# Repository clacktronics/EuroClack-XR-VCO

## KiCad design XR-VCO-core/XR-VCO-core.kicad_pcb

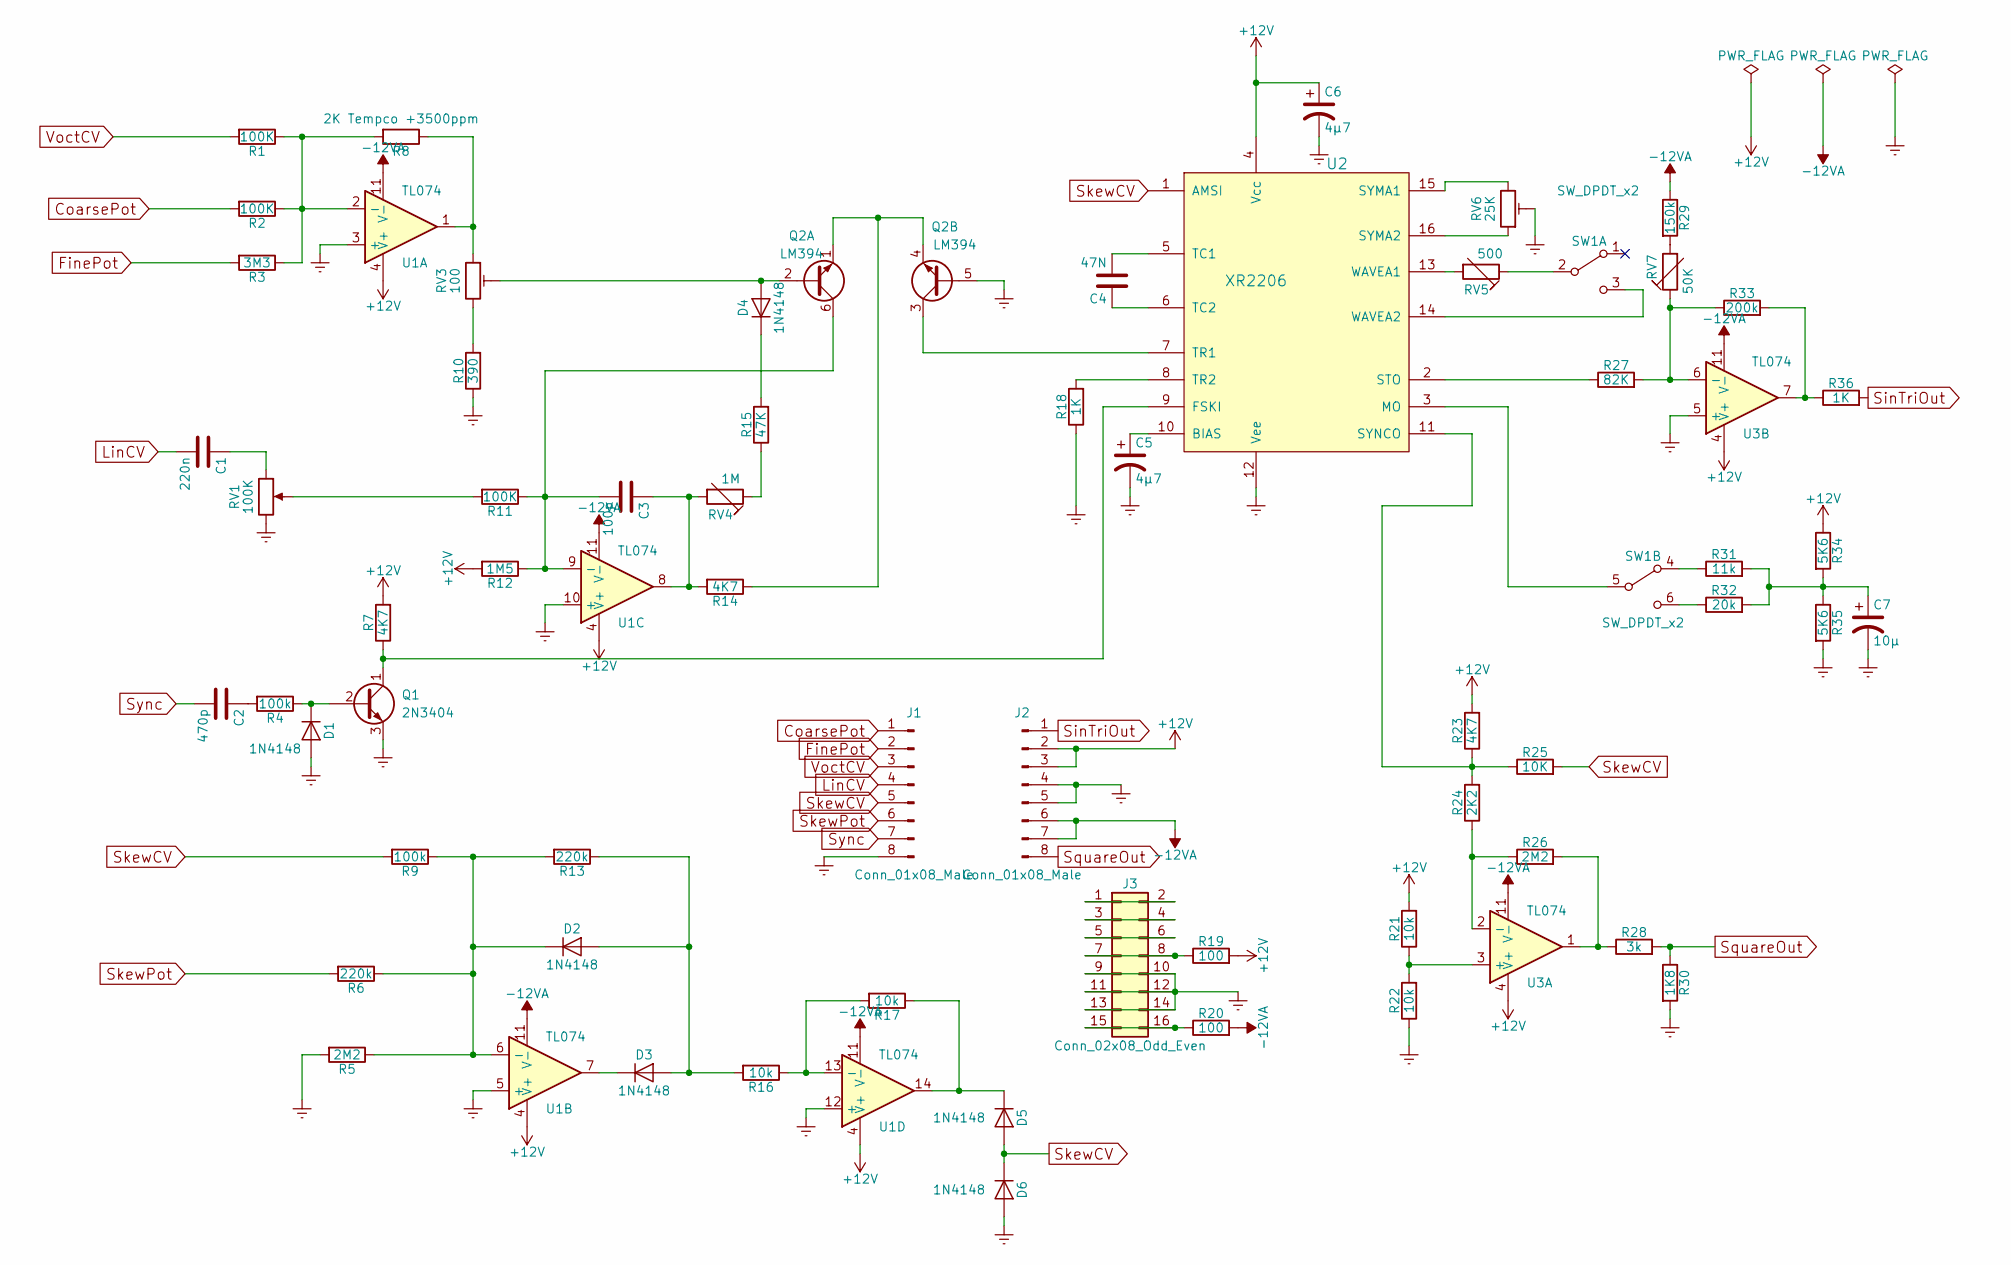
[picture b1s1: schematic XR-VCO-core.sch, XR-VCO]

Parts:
C1: 220n; C_Disc_D3.0mm_W1.6mm_P2.50mm
C2: 470p; C_Disc_D3.0mm_W1.6mm_P2.50mm
C3: 100p; C_Disc_D3.0mm_W1.6mm_P2.50mm
C4: 47N; C_Disc_D3.0mm_W1.6mm_P2.50mm
C5, C6: 4μ7; CP_Radial_D4.0mm_P1.50mm
C7: 10μ; CP_Radial_D4.0mm_P1.50mm
D1, D2, D3, D4, D5, D6: 1N4148; D_DO-35_SOD27_P7.62mm_Horizontal
J1, J2: Conn_01x08_Male; Pin_Header_Straight_1x08_Pitch2.54mm
J3: Conn_02x08_Odd_Even; IDC_Header_Straight_16pins
Q1: 2N3404; TO-92_Inline_Wide
Q2: LM394; DIP-8_W7.62mm_LongPads
R1, R2, R11: 100K; R_Axial_DIN0207_L6.3mm_D2.5mm_P10.16mm_Horizontal
R3: 3M3; R_Axial_DIN0207_L6.3mm_D2.5mm_P10.16mm_Horizontal
R4, R9: 100k; R_Axial_DIN0207_L6.3mm_D2.5mm_P10.16mm_Horizontal
R5, R26: 2M2; R_Axial_DIN0207_L6.3mm_D2.5mm_P10.16mm_Horizontal
R6, R13: 220k; R_Axial_DIN0207_L6.3mm_D2.5mm_P10.16mm_Horizontal
R7, R14, R23: 4K7; R_Axial_DIN0207_L6.3mm_D2.5mm_P10.16mm_Horizontal
R8: 2K Tempco +3500ppm; R_Axial_DIN0207_L6.3mm_D2.5mm_P10.16mm_Horizontal
R10: 390; R_Axial_DIN0207_L6.3mm_D2.5mm_P10.16mm_Horizontal
R12: 1M5; R_Axial_DIN0207_L6.3mm_D2.5mm_P10.16mm_Horizontal
R15: 47K; R_Axial_DIN0207_L6.3mm_D2.5mm_P10.16mm_Horizontal
R16, R17, R21, R22: 10k; R_Axial_DIN0207_L6.3mm_D2.5mm_P10.16mm_Horizontal
R18, R36: 1K; R_Axial_DIN0207_L6.3mm_D2.5mm_P10.16mm_Horizontal
R19, R20: 100; R_Axial_DIN0207_L6.3mm_D2.5mm_P10.16mm_Horizontal
R24: 2K2; R_Axial_DIN0207_L6.3mm_D2.5mm_P10.16mm_Horizontal
R25: 10K; R_Axial_DIN0207_L6.3mm_D2.5mm_P10.16mm_Horizontal
R27: 82K; R_Axial_DIN0207_L6.3mm_D2.5mm_P10.16mm_Horizontal
R28: 3k; R_Axial_DIN0207_L6.3mm_D2.5mm_P10.16mm_Horizontal
R29: 150k; R_Axial_DIN0207_L6.3mm_D2.5mm_P10.16mm_Horizontal
R30: 1K8; R_Axial_DIN0207_L6.3mm_D2.5mm_P10.16mm_Horizontal
R31: 11k; R_Axial_DIN0207_L6.3mm_D2.5mm_P10.16mm_Horizontal
R32: 20k; R_Axial_DIN0207_L6.3mm_D2.5mm_P10.16mm_Horizontal
R33: 200k; R_Axial_DIN0207_L6.3mm_D2.5mm_P10.16mm_Horizontal
R34, R35: 5K6; R_Axial_DIN0207_L6.3mm_D2.5mm_P10.16mm_Horizontal
RV1: 100K; Potentiometer_Trimmer_Bourns_PV36W
RV3: 100; Potentiometer_Trimmer_Bourns_PV36W
RV4: 1M; Potentiometer_Trimmer_Bourns_PV36W
RV5: 500; Potentiometer_Trimmer_Bourns_PV36W
RV6: 25K; Potentiometer_Trimmer_Bourns_PV36W
RV7: 50K; Potentiometer_Trimmer_Bourns_PV36W
SW1: SW_DPDT_x2; SW_DIP_x3_Slide
U1: TL074; DIP-14_W7.62mm_LongPads
U2: XR2206; DIP-16_W7.62mm_Socket_LongPads
U3: TL074; DIP-14_W7.62mm_Socket_LongPads

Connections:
+12V: C6.1, J2.2, J2.3, R7.2, R12.2, R19.2, R21.2, R23.2, R34.1, U1.4 (V+), U2.4 (Vcc), U3.4 (V+)
-12VA: J2.6, J2.7, R20.2, R29.1, U1.11 (V-), U3.11 (V-)
CoarsePot: J1.1, R2.2
Earth: C5.2, C6.2, C7.2, D1.2 (A), D6.2 (A), J1.8, J2.4, J2.5, J3.9, J3.10, J3.11, J3.12, J3.13, J3.14, Q1.3 (E), Q2.5 (B2), R5.2, R10.1, R18.1, R22.1, R30.2, R35.2, RV1.3, RV6.2, U1.3 (+), U1.5 (+), U1.10 (+), U1.12 (+), U2.12 (Vee), U3.5 (+)
FinePot: J1.2, R3.2
LinCV: C1.2, J1.4
unnamed: C1.1, RV1.1
unnamed: C2.1, R4.2
unnamed: C3.1, R14.2, RV4.2, U1.8
unnamed: C3.2, Q2.6 (C1), R11.1, R12.1, U1.9 (-)
unnamed: C4.1, U2.6 (TC2)
unnamed: C4.2, U2.5 (TC1)
unnamed: C5.1, U2.10 (BIAS)
unnamed: C7.1, R31.2, R32.2, R34.2, R35.1
unnamed: D1.1 (K), Q1.2 (B), R4.1
unnamed: D2.1 (K), R5.1, R6.1, R9.1, R13.2, U1.6 (-)
unnamed: D2.2 (A), D3.2 (A), R13.1, R16.2
unnamed: D3.1 (K), U1.7
unnamed: D4.1 (K), R15.2
unnamed: D4.2 (A), Q2.2 (B1), RV3.2
unnamed: D5.1 (K), R17.1, U1.14
unnamed: J3.1, J3.2
unnamed: J3.3, J3.4
unnamed: J3.5, J3.6
unnamed: J3.7, J3.8, R19.1
unnamed: J3.15, J3.16, R20.1
unnamed: Q1.1 (C), R7.1, U2.9 (FSKI)
unnamed: Q2.1 (E1), Q2.4 (E2), R14.1
unnamed: Q2.3 (C2), U2.7 (TR1)
unnamed: R1.1, R2.1, R3.1, R8.2, U1.2 (-)
unnamed: R8.1, RV3.1, U1.1
unnamed: R10.2, RV3.3
unnamed: R11.2, RV1.2
unnamed: R15.1, RV4.1
unnamed: R16.1, R17.2, U1.13 (-)
unnamed: R18.2, U2.8 (TR2)
unnamed: R21.1, R22.2, U3.3 (+)
unnamed: R23.1, R24.2, R25.1, U2.11 (SYNCO)
unnamed: R24.1, R26.1, U3.2 (-)
unnamed: R26.2, R28.1, U3.1
unnamed: R27.1, U2.2 (STO)
unnamed: R27.2, R33.1, RV7.1, U3.6 (-)
unnamed: R29.2, RV7.2
unnamed: R31.1, SW1.4 (A)
unnamed: R32.1, SW1.6 (C)
unnamed: R33.2, R36.1, U3.7
unnamed: RV5.1, SW1.2 (B)
unnamed: RV5.2, U2.13 (WAVEA1)
unnamed: RV6.1, U2.16 (SYMA2)
unnamed: RV6.3, U2.15 (SYMA1)
unnamed: SW1.3 (C), U2.14 (WAVEA2)
unnamed: SW1.5 (B), U2.3 (MO)
SinTriOut: J2.1, R36.2
SkewCV: D5.2 (A), D6.1 (K), J1.5, R9.2, R25.2, U2.1 (AMSI)
SkewPot: J1.6, R6.2
SquareOut: J2.8, R28.2, R30.1
Sync: C2.2, J1.7
VoctCV: J1.3, R1.2

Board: 2 copper layers, 64 parts (1 on the bottom side), 58 nets, no tracks yet.

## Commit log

2017-12-14 initial
2017-12-29 Reshuffling and adding docs
2017-12-29 Index should be html
2017-12-30 Trying to make pages work
2017-12-30 tweak
2017-12-30 test
2017-12-30 Trying to get docs to work
2018-01-03 trying to do readme
2018-01-03 Simpler index
2018-01-03 CSS edit
2018-01-03 CSS edits again
